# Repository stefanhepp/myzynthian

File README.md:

README
------

This project is a Zynthian case build with the following features:

- The hardware is based on:
    - Raspberry Pi 3/4 with passive cooler
    - IQaudio DAC+ audio shield
    - 7" LCD DSI Touchscreen
- Custom IO expander board for MIDI, 4x encoders

Sources
-------

The IO Expander board design is based on Zynthian's Zynaptic v3 design:
https://github.com/zynthian/zynthian-hw

The FreeCAD design uses the following models:
- 7" Display Reference Model: From Printables User Clough42: 
  https://www.printables.com/model/202234-official-raspberry-pi-7-touch-screen-reference-mod
- Raspberry PI 4: From GrabCAD User Zahid Salman: https://grabcad.com/library/raspberry-pi-model-3-4-cooling-1
- HifiBerry: From GrabCAD User Alain Gourvès: https://grabcad.com/library/hifiberry-dac-1
- Rotary Encoder: From GrabCAD User joel bennett: https://grabcad.com/library/rotary-encoder-ky-040-2
- DIN 5F Socket: From GrabCAD User Leininger Stéphane: https://grabcad.com/library/din-5f-type-mab-1
- LED 3mm: From GrabCAD User John Walker: https://grabcad.com/library/led-3mm-with-housing-1 

License
-------
Shield: [![CC BY-SA 4.0][cc-by-sa-shield]][cc-by-sa]

This work is licensed under a
[Creative Commons Attribution-ShareAlike 4.0 International License][cc-by-sa].

[![CC BY-SA 4.0][cc-by-sa-image]][cc-by-sa]

[cc-by-sa]: http://creativecommons.org/licenses/by-sa/4.0/
[cc-by-sa-image]: https://licensebuttons.net/l/by-sa/4.0/88x31.png
[cc-by-sa-shield]: https://img.shields.io/badge/License-CC%20BY--SA%204.0-lightgrey.svg

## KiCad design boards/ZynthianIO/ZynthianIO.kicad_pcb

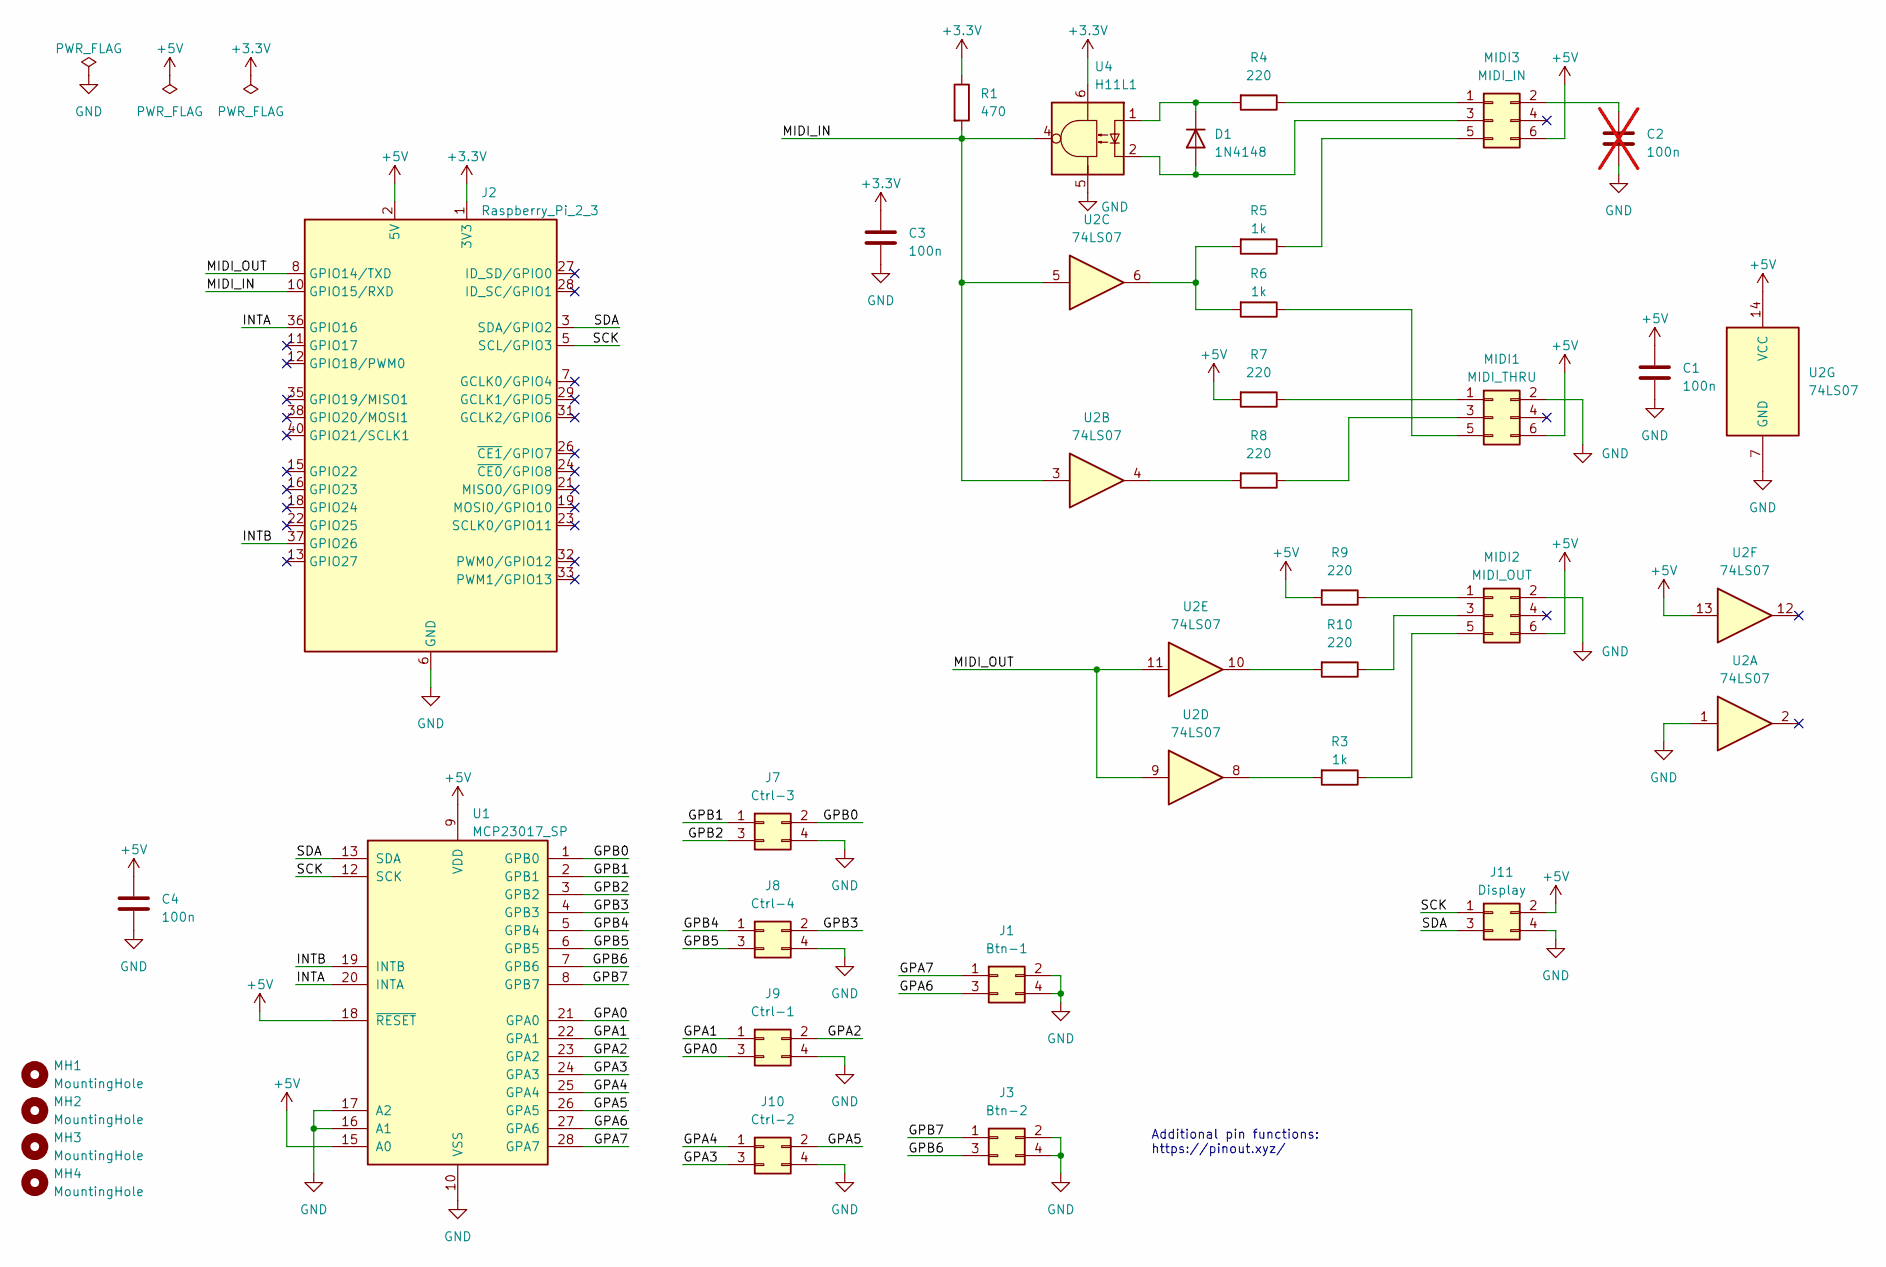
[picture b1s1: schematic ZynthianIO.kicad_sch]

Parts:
C1, C3, C4: 100n; C_Disc_D5.0mm_W2.5mm_P5.00mm
C2: 100n; C_Disc_D5.0mm_W2.5mm_P5.00mm; not fitted
D1: 1N4148; D_DO-35_SOD27_P7.62mm_Horizontal
J1: Btn-1; PinHeader_2x02_P2.54mm_Horizontal
J2: Raspberry_Pi_2_3; PinSocket_2x20_P2.54mm_Vertical
J3: Btn-2; PinHeader_2x02_P2.54mm_Horizontal
J7: Ctrl-3; PinHeader_2x02_P2.54mm_Horizontal
J8: Ctrl-4; PinHeader_2x02_P2.54mm_Horizontal
J9: Ctrl-1; PinHeader_2x02_P2.54mm_Horizontal
J10: Ctrl-2; PinHeader_2x02_P2.54mm_Horizontal
J11: Display; PinHeader_2x02_P2.54mm_Horizontal
MH1, MH2, MH3, MH4: MountingHole; MountingHole_2.7mm_M2.5
MIDI1: MIDI_THRU; PinHeader_2x03_P2.54mm_Horizontal
MIDI2: MIDI_OUT; PinHeader_2x03_P2.54mm_Horizontal
MIDI3: MIDI_IN; PinHeader_2x03_P2.54mm_Horizontal
R1: 470; R_Axial_DIN0207_L6.3mm_D2.5mm_P10.16mm_Horizontal
R3, R5, R6: 1k; R_Axial_DIN0207_L6.3mm_D2.5mm_P10.16mm_Horizontal
R4, R7, R8, R9, R10: 220; R_Axial_DIN0207_L6.3mm_D2.5mm_P10.16mm_Horizontal
U1: MCP23017_SP; DIP-28_W7.62mm
U2: 74LS07; DIP-14_W7.62mm
U4: H11L1; DIP-6_W7.62mm

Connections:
+3.3V: C3.1, J2.1 (3V3), J2.17 (3V3), R1.1, U4.6
+5V: C1.1, C4.1, J2.2 (5V), J2.4 (5V), J11.2, MIDI1.6, MIDI2.6, MIDI3.6, R7.2, R9.2, U1.9 (VDD), U1.15 (A0), U1.18 (~RESET), U2.13, U2.14 (VCC)
/GPA0: J9.3, U1.21 (GPA0)
/GPA1: J9.1, U1.22 (GPA1)
/GPA2: J9.2, U1.23 (GPA2)
/GPA3: J10.3, U1.24 (GPA3)
/GPA4: J10.1, U1.25 (GPA4)
/GPA5: J10.2, U1.26 (GPA5)
/GPA6: J1.3, U1.27 (GPA6)
/GPA7: J1.1, U1.28 (GPA7)
/GPB0: J7.2, U1.1 (GPB0)
/GPB1: J7.1, U1.2 (GPB1)
/GPB2: J7.3, U1.3 (GPB2)
/GPB3: J8.2, U1.4 (GPB3)
/GPB4: J8.1, U1.5 (GPB4)
/GPB5: J8.3, U1.6 (GPB5)
/GPB6: J3.3, U1.7 (GPB6)
/GPB7: J3.1, U1.8 (GPB7)
/INTA: J2.36 (GPIO16), U1.20 (INTA)
/INTB: J2.37 (GPIO26), U1.19 (INTB)
/MIDI_IN: J2.10 (GPIO15/RXD), R1.2, U2.3, U2.5, U4.4
/MIDI_OUT: J2.8 (GPIO14/TXD), U2.9, U2.11
/SCK: J2.5 (SCL/GPIO3), J11.1, U1.12 (SCK)
/SDA: J2.3 (SDA/GPIO2), J11.3, U1.13 (SDA)
GND: C1.2, C2.2, C3.2, C4.2, J1.2, J1.4, J2.6 (GND), J2.9 (GND), J2.14 (GND), J2.20 (GND), J2.25 (GND), J2.30 (GND), J2.34 (GND), J2.39 (GND), J3.2, J3.4, J7.4, J8.4, J9.4, J10.4, J11.4, MIDI1.2, MIDI2.2, U1.10 (VSS), U1.16 (A1), U1.17 (A2), U2.1, U2.7 (GND), U4.5
unnamed: D1.2 (A), MIDI3.3, U4.2
unnamed: D1.1 (K), R4.2, U4.1
unnamed: MIDI1.1, R7.1
unnamed: MIDI1.3, R8.1
unnamed: MIDI1.5, R6.1
unnamed: MIDI2.1, R9.1
unnamed: MIDI2.3, R10.1
unnamed: MIDI2.5, R3.1
unnamed: MIDI3.1, R4.1
unnamed: C2.1, MIDI3.2
unnamed: MIDI3.5, R5.1
unnamed: R3.2, U2.8
unnamed: R5.2, R6.2, U2.6
unnamed: R8.2, U2.4
unnamed: R10.2, U2.10

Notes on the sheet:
Additional pin functions: https://pinout.xyz/

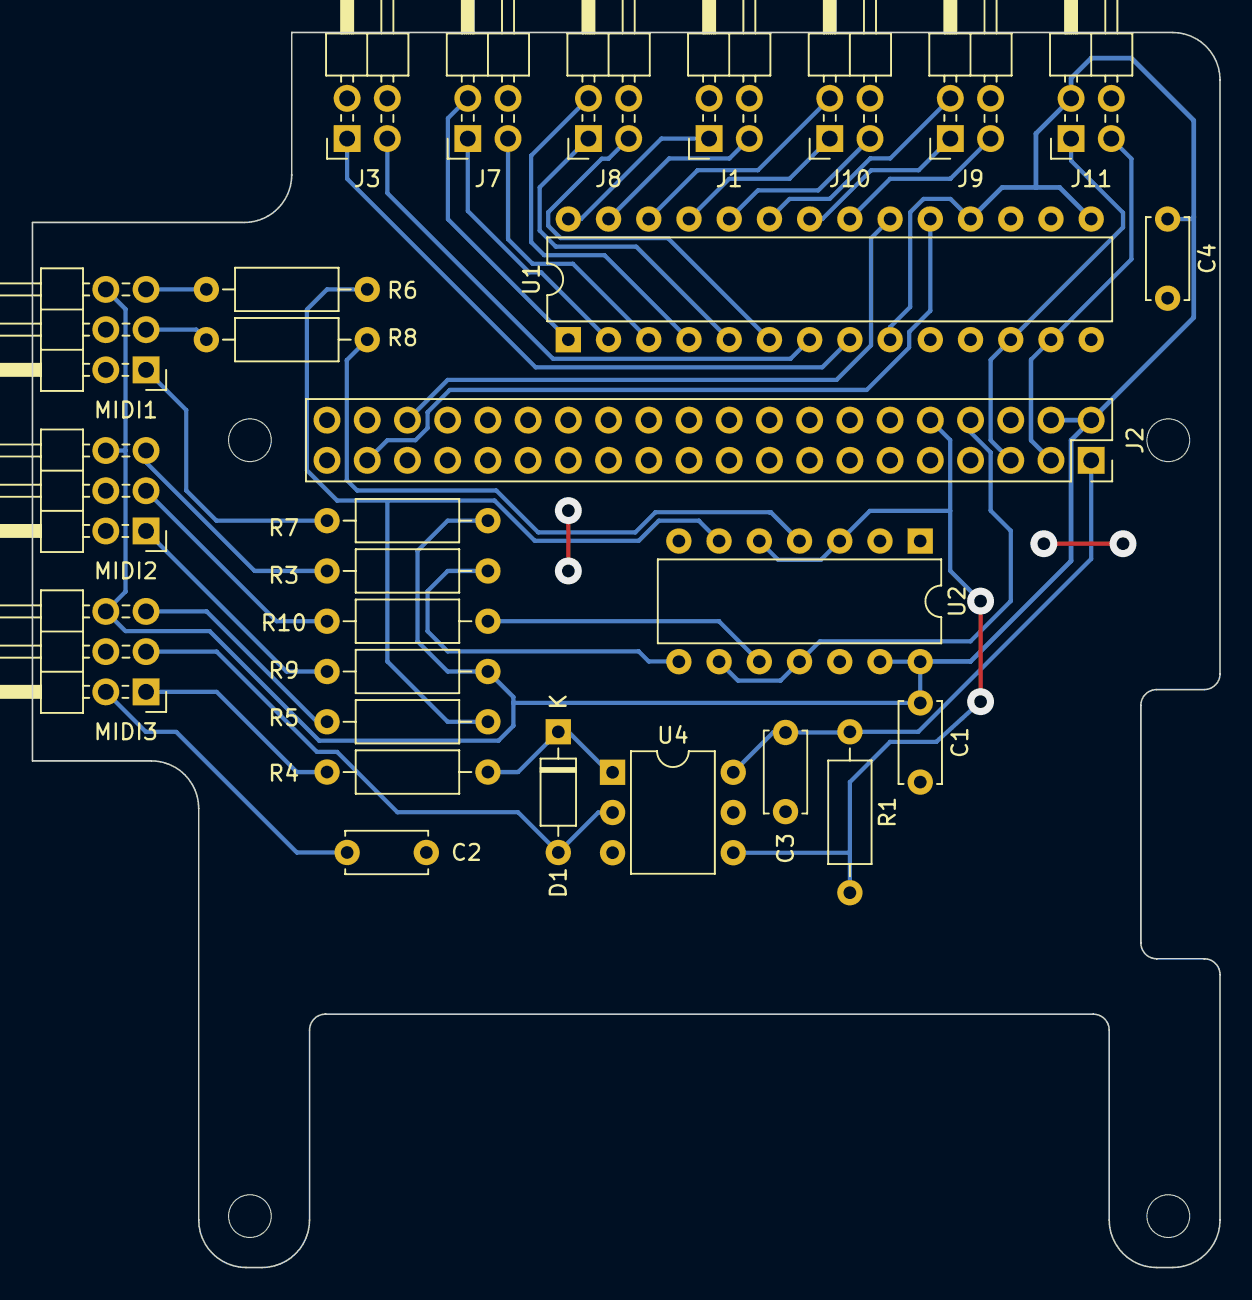
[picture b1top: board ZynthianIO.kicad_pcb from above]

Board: 2 copper layers, 75.0 x 78.0 mm, 32 parts (0 on the bottom side), 40 nets.

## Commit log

2023-02-22 Added initial readme
2023-02-22 Fixed readme formatting
2023-04-16 First IO expander board design, including PCB
2023-04-16 Added IO Expander 3D model and connectors to case design, added references to sources.
2023-04-16 Added LED for MIDI connectors
2023-04-17 Removed temporary and local KiCAD files
2023-04-18 Updated IO expander board with Raspberry HAT template PCB design
2023-04-18 Fixing several layout issues due to KiCAD 7.0.2/Linux update
2023-04-18 Updated 3D case design with new IO expander PCB
2023-10-24 Some first drawings for Zynthian case
2024-01-13 Ignore new FreeCAD backup files
2024-01-13 Added some cover design for Zynthian case design
2024-01-23 Initial new Boutique formfactor case design
2024-01-28 Fixed FreeCAD sketches, fixed display mounting position
2024-01-28 Added top cover screw posts
2024-01-28 Finished Boutique case design, added Step files
2024-01-29 Fixed several cutout clearances, added additional airvents
2024-01-30 Fixed cinch connector cutout location
2024-01-31 New ZynthianIO board design for Boutique case
2024-02-13 Fixed MIDI interfaces
2024-03-03 Updated to KiCAD 8, use H11L1 as optocoupler
2024-03-03 Ignore small connection bridge from DRC
2024-03-13 Added PCB dimensions
2024-03-14 Using 74LS07 OC buffer to avoid excessive LED currents
2024-04-19 Several fixes to reinfoce case
2024-04-20 Fixed position of Raspberry Pi due to larger wall thickness
2024-04-21 Added chamfer to top cover
2024-04-25 Fixed resistor footprints and USB cutout locations
2024-04-25 Fixed footprint reference locations
2024-05-01 Fixed resistor footprints, design rules update
2024-05-05 Fixed locked ground plane
2024-05-08 Added PCB spacer for IO board
2024-05-08 Fixed ground plane connection, change 23017 address from 0x24 to 0x21
2024-05-12 Fixed rotary switches connections
